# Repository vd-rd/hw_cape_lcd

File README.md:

# hw_cape_lcd
LCD module for embedded projects

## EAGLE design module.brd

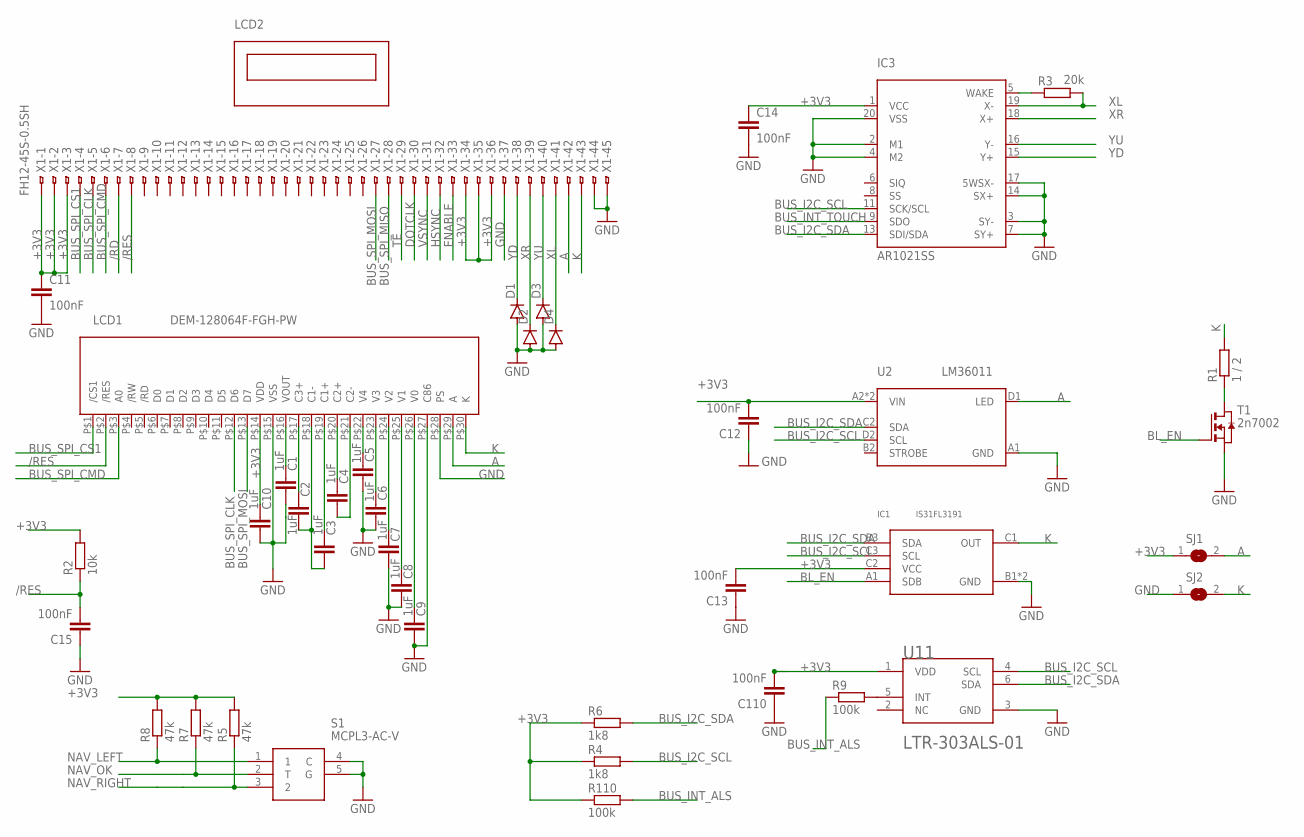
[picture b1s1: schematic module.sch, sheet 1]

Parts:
C1, C2, C3, C4, C5, C6, C7, C8, C9, C10: 1uF; C0805
C11, C12, C13, C14, C15, C110: 100nF; C0603
D1, D2, D3, D4: DIODE-SOD323-R; SOD323-R
IC1: IS31FL3191; BGA9N40P3X3_133X133X56N
IC3: AR1021SS; SOP65P780X200-20N
LCD1: DEM-128064F-FGH-PW; DEM128064FFGH
LCD2: DEM-230320K-TMH-PW; DEM-240320K-TMH
R1: 1 / 2; R0603
R2: 10k; R0603
R3: 20k; R0603
R4, R6: 1k8; R0603
R5, R7, R8: 47k; R0603
R9, R110: 100k; R0603
S1: MCPL3-AC-V
SJ1, SJ2: SJ
T1: 2n7002; SOT-23
U2: LM36011; BGA8C35P2X4_151X80X50
U11: LITE-ON_LTR-303ALS-01LITE-ON_LTR-303ALS-01_0_0; LITE-ON_LTR-303ALS-01_0
X1: FH12-45S-0.5SH

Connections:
+3V3: C10.1, C11.1, C12.2, C13.2, C14.1, C110.2, IC1.C2 (VCC), IC3.1 (VCC), LCD1.P$14 (VDD), R2.2, R4.1, R5.2, R6.1, R7.2, R8.2, R110.1, SJ1.1, U2.A2 (VIN), U2.C1 (VIN), U11.1 (VDD), X1.1, X1.2, X1.3, X1.34, X1.35, X1.36; also elsewhere on the board
/RD: X1.7
/RES: C15.2, LCD1.P$2 (/RES), R2.1, X1.8
A: LCD1.P$29 (A), SJ1.2, U2.D1 (LED), X1.42
BL_EN: IC1.A1 (SDB), T1.3 (G)
BUS_I2C_SCL: IC1.C3 (SCL), IC3.11 (SCK/SCL), R4.2, U2.D2 (SCL), U11.4 (SCL)
BUS_I2C_SDA: IC1.B3 (SDA), IC3.13 (SDI/SDA), R6.2, U2.C2 (SDA), U11.6 (SDA)
BUS_INT_ALS: R9.1, R110.2
BUS_INT_TOUCH: IC3.9 (SDO)
BUS_SPI_CLK: LCD1.P$12 (D6), X1.5
BUS_SPI_CMD: LCD1.P$3 (A0), X1.6
BUS_SPI_CS1: LCD1.P$1 (/CS1), X1.4
BUS_SPI_MISO: X1.28
BUS_SPI_MOSI: LCD1.P$13 (D7), X1.27
DOTCLK: X1.30
ENABLE: X1.33
GND: C1.2, C5.2, C6.2, C7.2, C8.2, C9.2, C10.2, C11.2, C12.1, C13.1, C14.2, C15.1, C110.1, D1.A, D2.A, D3.A, D4.A, IC1.B1 (GND), IC1.B2 (GND), IC3.2 (M1), IC3.3 (SY-), IC3.4 (M2), IC3.7 (SY+), IC3.14 (SX+), IC3.17 (5WSX-), IC3.20 (VSS), LCD1.P$15 (VSS), LCD1.P$27 (C86), LCD1.P$28 (PS), S1.4 (C), S1.5 (G), SJ2.1, T1.2 (S), U2.A1 (GND), U11.3 (GND), X1.37, X1.44, X1.45; also elsewhere on the board
HSYNC: X1.32
K: IC1.C1 (OUT), LCD1.P$30 (K), R1.2, SJ2.2, X1.43
unnamed: C1.1, LCD1.P$16 (VOUT)
unnamed: C2.1, LCD1.P$17 (C3+)
unnamed: C2.2, C3.2, LCD1.P$18 (C1-)
unnamed: C3.1, LCD1.P$19 (C1+)
unnamed: C4.1, LCD1.P$20 (C2+)
unnamed: C4.2, LCD1.P$21 (C2-)
unnamed: C5.1, LCD1.P$22 (V4)
unnamed: C6.1, LCD1.P$23 (V3)
unnamed: C7.1, LCD1.P$24 (V2)
unnamed: C8.1, LCD1.P$25 (V1)
unnamed: C9.1, LCD1.P$26 (V0)
unnamed: R1.1, T1.1 (D)
unnamed: R9.2, U11.5 (INT)
unnamed: IC3.5 (WAKE), R3.1
NAV_LEFT: R8.1, S1.1
NAV_OK: R7.1, S1.2 (T)
NAV_RIGHT: R5.1, S1.3 (2)
TE: X1.29
VSYNC: X1.31
XL: D4.C, IC3.19 (X-), R3.2, X1.41
XR: D2.C, IC3.18 (X+), X1.39
YD: D1.C, IC3.15 (Y+), X1.38
YU: D3.C, IC3.16 (Y-), X1.40

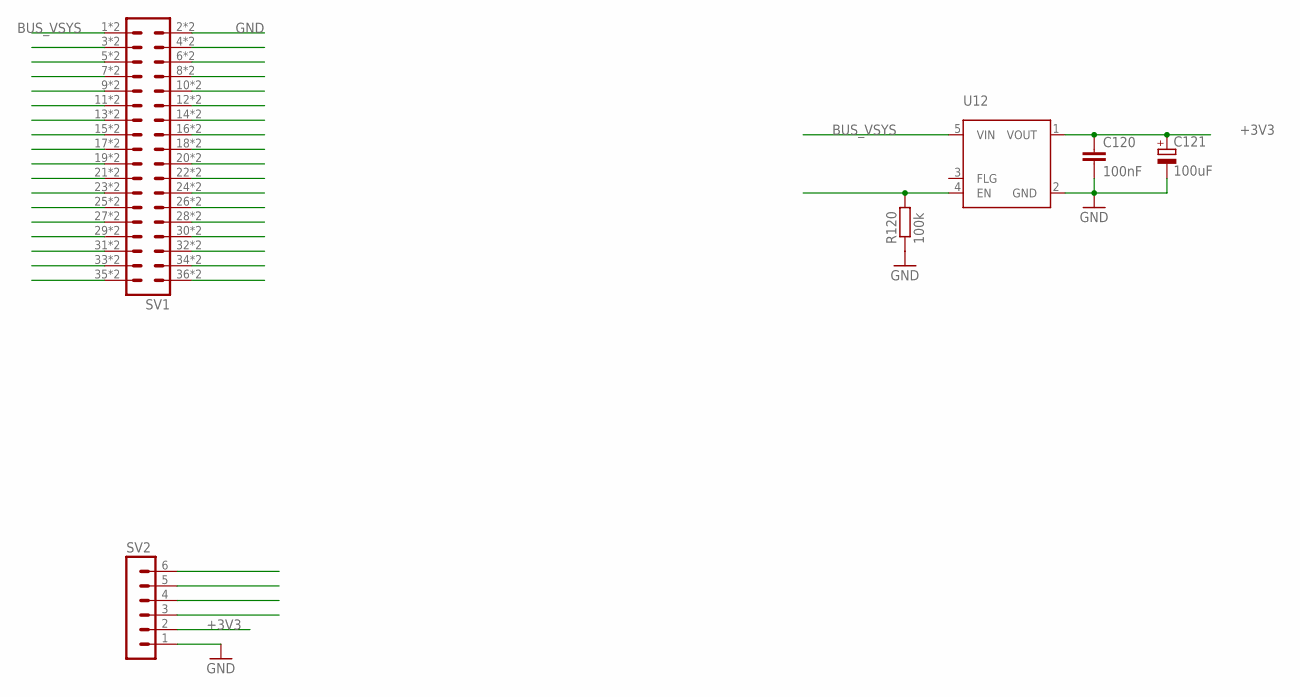
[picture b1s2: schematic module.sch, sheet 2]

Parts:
C120: 100nF; C0402
C121: 100uF; SMC_C
R120: 100k; R0402
SV1: MA18-2SMT; MA18-2-SMT
SV2: CONN-1X6; MA06-1
U12: AP22802; SOT25

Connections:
+3V3: C120.1, C121.+, SV2.2, U12.1 (VOUT); also elsewhere on the board
BUS_VSYS: SV1.1, SV1.P$1 (1), U12.5 (VIN)
GND: C120.2, C121.-, R120.1, SV1.2, SV1.P$2 (2), SV2.1, U12.2 (GND); also elsewhere on the board
unnamed: R120.2, U12.4 (EN)
unnamed: SV1.3, SV1.P$3 (3)
unnamed: SV1.5, SV1.P$5 (5)
unnamed: SV1.4, SV1.P$4 (4)
unnamed: SV1.6, SV1.P$6 (6)
unnamed: SV1.7, SV1.P$7 (7)
unnamed: SV1.9, SV1.P$9 (9)
unnamed: SV1.8, SV1.P$8 (8)
unnamed: SV1.10, SV1.P$10 (10)
unnamed: SV1.11, SV1.P$11 (11)
unnamed: SV1.13, SV1.P$13 (13)
unnamed: SV1.15, SV1.P$15 (15)
unnamed: SV1.12, SV1.P$12 (12)
unnamed: SV1.14, SV1.P$14 (14)
unnamed: SV1.16, SV1.P$16 (16)
unnamed: SV1.17, SV1.P$17 (17)
unnamed: SV1.19, SV1.P$19 (19)
unnamed: SV1.18, SV1.P$18 (18)
unnamed: SV1.20, SV1.P$20 (20)
unnamed: SV1.21, SV1.P$21 (21)
unnamed: SV1.23, SV1.P$23 (23)
unnamed: SV1.25, SV1.P$25 (25)
unnamed: SV1.22, SV1.P$22 (22)
unnamed: SV1.24, SV1.P$24 (24)
unnamed: SV1.26, SV1.P$26 (26)
unnamed: SV1.27, SV1.P$27 (27)
unnamed: SV1.29, SV1.P$29 (29)
unnamed: SV1.28, SV1.P$28 (28)
unnamed: SV1.30, SV1.P$30 (30)
unnamed: SV1.31, SV1.P$31 (31)
unnamed: SV1.33, SV1.P$33 (33)
unnamed: SV1.32, SV1.P$32 (32)
unnamed: SV1.34, SV1.P$34 (34)
unnamed: SV1.35, SV1.P$35 (35)
unnamed: SV1.36, SV1.P$36 (36)

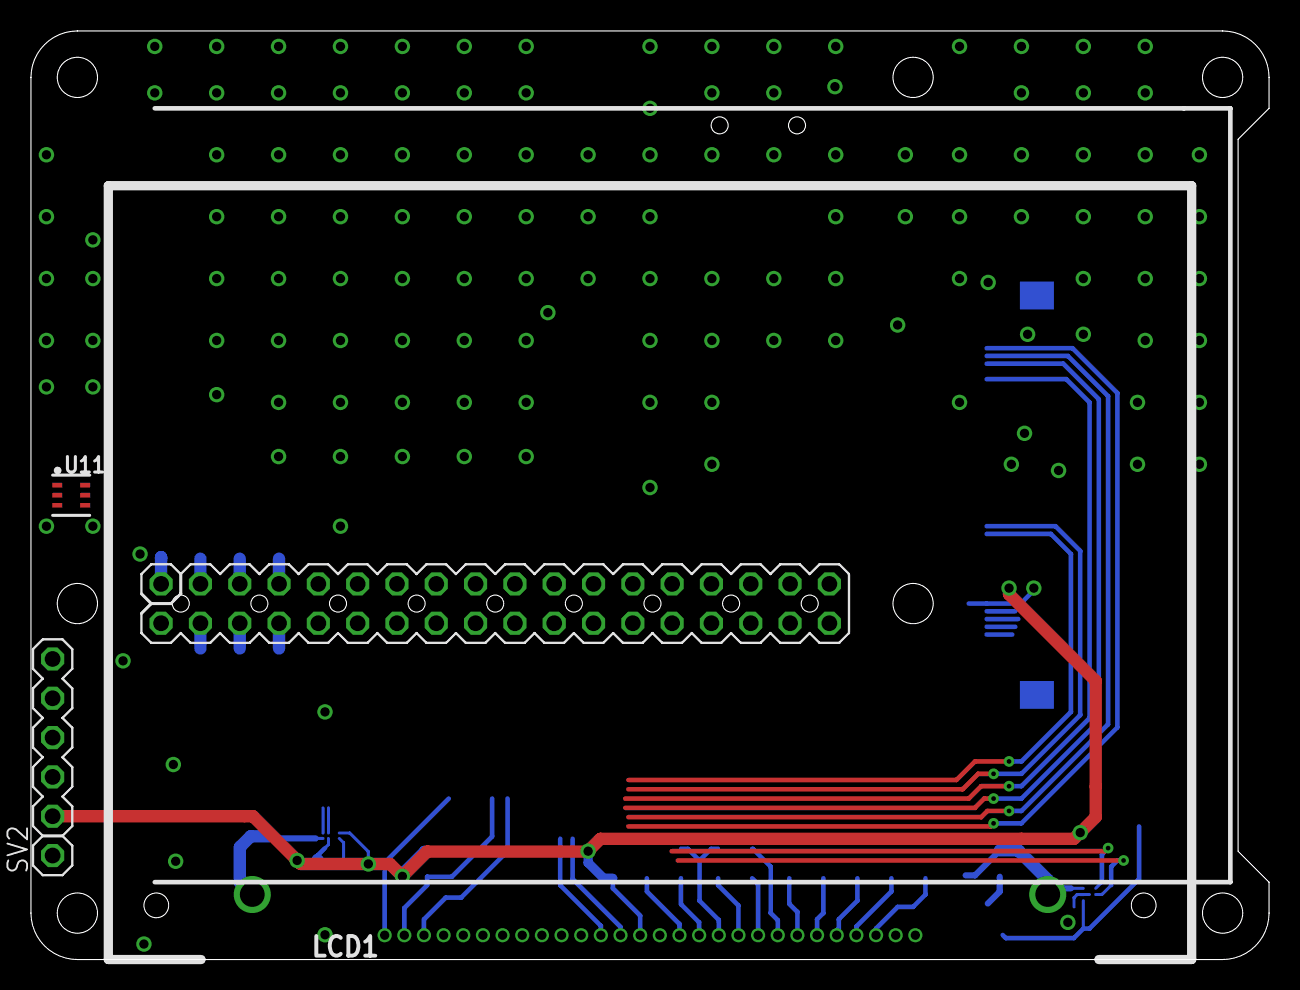
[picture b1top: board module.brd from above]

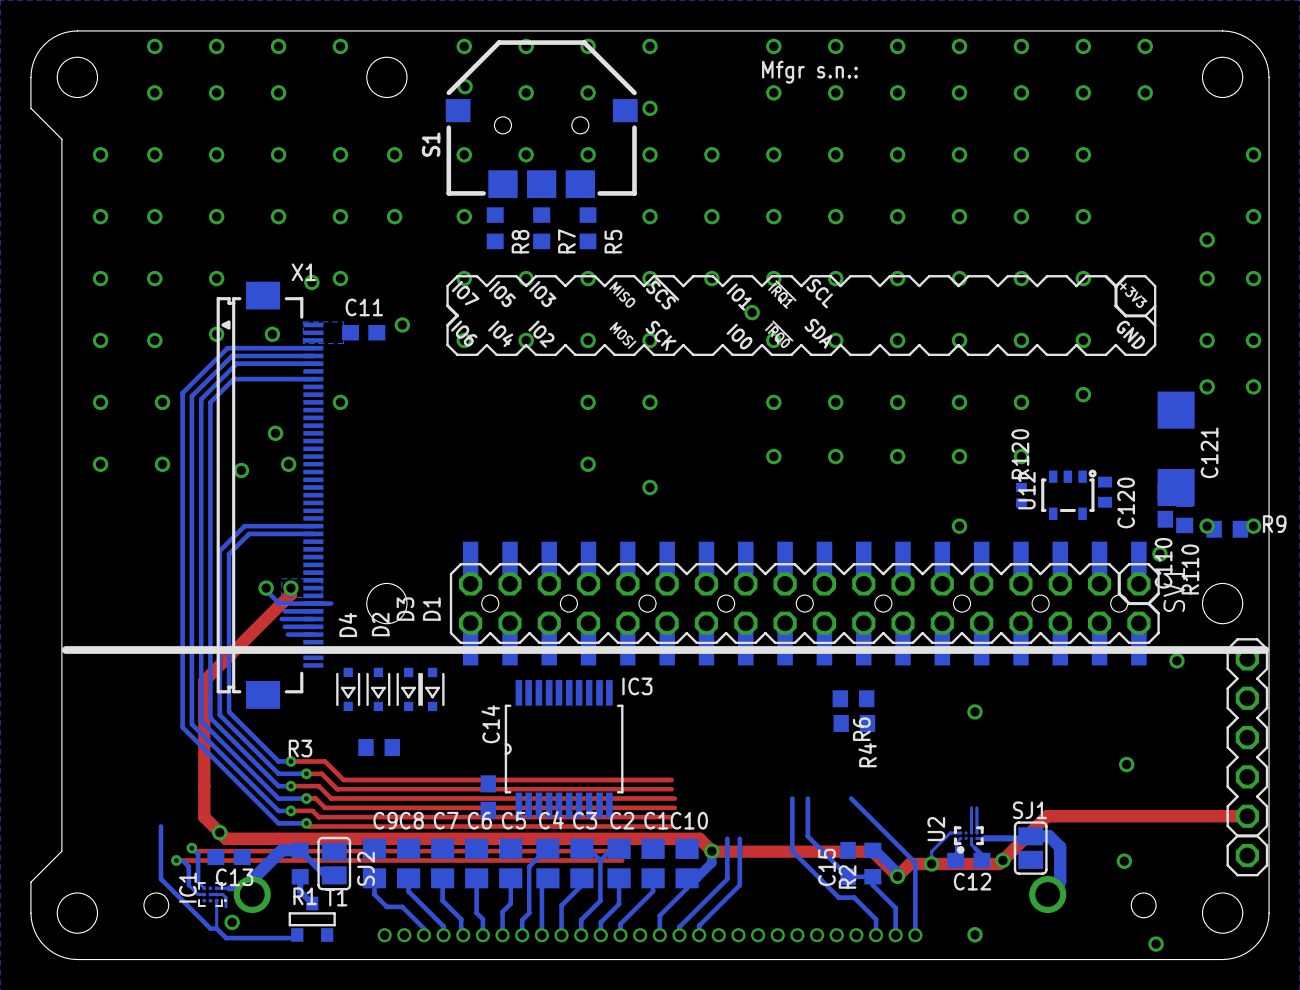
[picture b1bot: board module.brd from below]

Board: 2 copper layers, 80.0 x 60.0 mm, 47 parts (43 on the bottom side), 70 nets.

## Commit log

2019-05-22 project: defined structure
2019-05-22 board: established floorplan and features
2022-04-17 switch to kicad
2022-04-17 add light sensor
2022-04-18 add routing for lcd connector
2022-04-25 defined shape for fascontek 3in lcd
2022-04-29 move from generic module to folders
